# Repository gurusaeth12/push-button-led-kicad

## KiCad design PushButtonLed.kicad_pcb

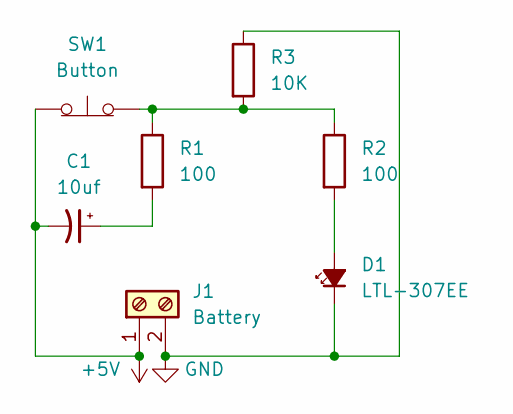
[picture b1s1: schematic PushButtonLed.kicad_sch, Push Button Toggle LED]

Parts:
C1: 10uf; CP_Radial_D4.0mm_P1.50mm
D1: LTL-307EE; LED_D3.0mm_FlatTop
J1: Battery; TestPoint_2Pads_Pitch5.08mm_Drill1.3mm
R1, R2: 100; R_Axial_DIN0204_L3.6mm_D1.6mm_P1.90mm_Vertical
R3: 10K; R_Axial_DIN0204_L3.6mm_D1.6mm_P5.08mm_Horizontal
SW1: Button; SW_PUSH_6mm

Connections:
+5V: C1.2, J1.1, SW1.1 (A)
GND: D1.1 (K), J1.2, R3.1
unnamed: C1.1, R1.2
unnamed: D1.2 (A), R2.2
unnamed: R1.1, R2.1, R3.2, SW1.2 (B)

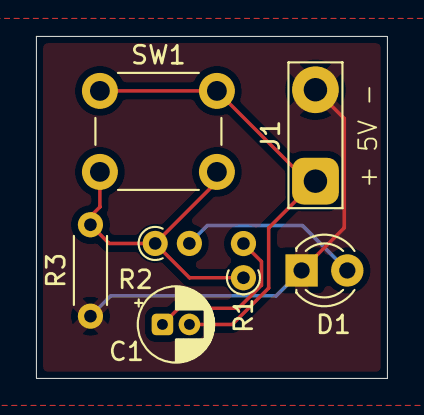
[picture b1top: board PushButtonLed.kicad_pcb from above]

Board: 2 copper layers, 19.5 x 19.0 mm, 7 parts (0 on the bottom side), 5 nets.

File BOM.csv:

Reference,Value / Description,Quantity,Notes
J1,Battery / 2-pin input connector,1,Power input; confirm connector footprint before ordering
SW1,Push button,1,Momentary switch
D1,LTL-307EE LED,1,LED part/value as shown in schematic
R1,100 ohm resistor,1,As specified in schematic
R2,100 ohm resistor,1,As specified in schematic
R3,10 kΩ resistor,1,As specified in schematic
C1,10 µF polarized capacitor,1,Check polarity and footprint before assembly
